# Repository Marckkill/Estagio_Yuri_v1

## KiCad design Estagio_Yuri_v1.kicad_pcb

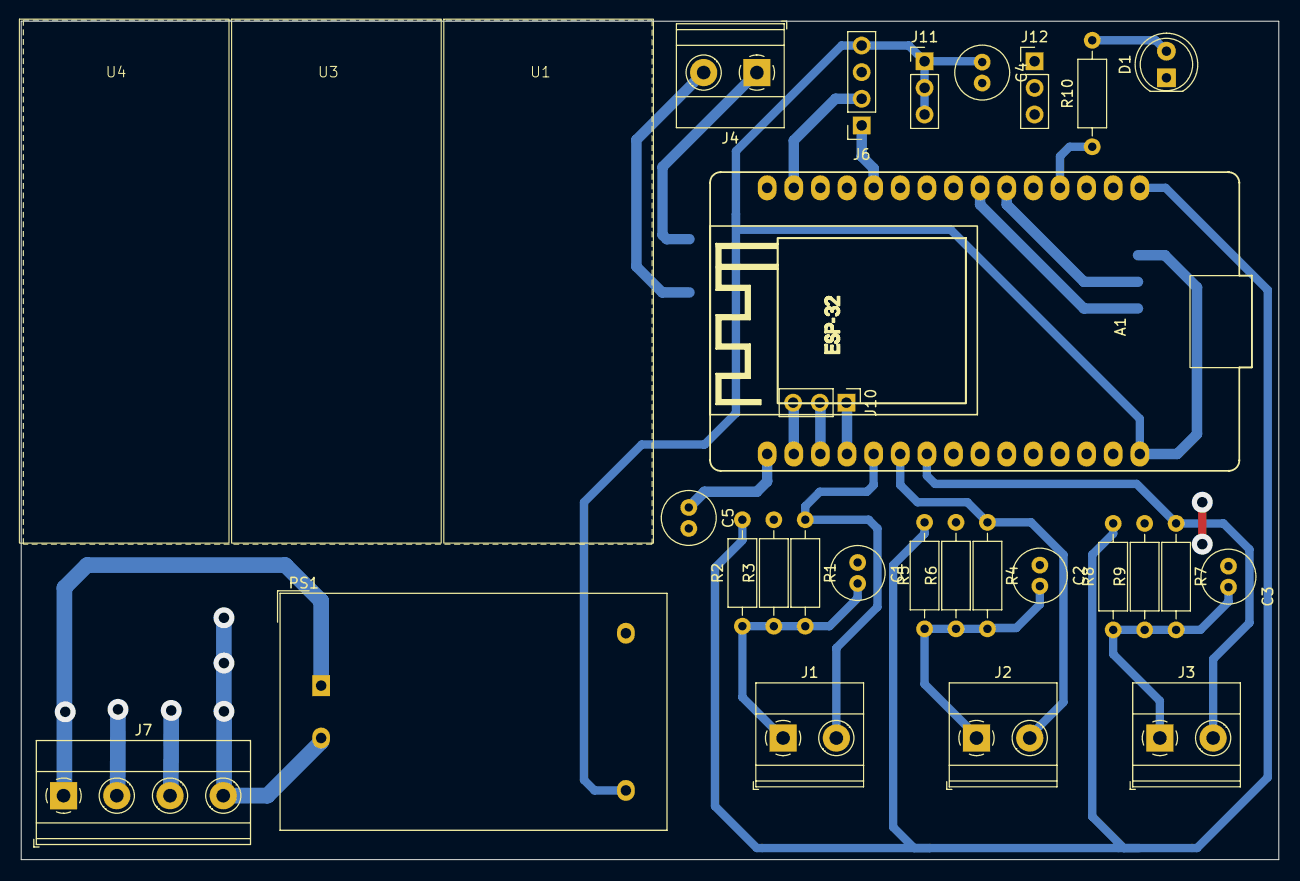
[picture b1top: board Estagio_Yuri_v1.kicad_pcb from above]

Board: 2 copper layers, 120.0 x 80.0 mm, 31 parts (1 on the bottom side), 23 nets.

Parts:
A1: ESP32; DOIT_ESP32_DEVKIT_30Pins
C1, C2, C3: 10u; C_Radial_D5.0mm_H11.0mm_P2.00mm
C4, C5: C; C_Radial_D5.0mm_H11.0mm_P2.00mm
D1: LED; LED_D5.0mm
J1, J2, J3, J4: EASTRON; TerminalBlock_Phoenix_MKDS-1,5-2-5.08_1x02_P5.08mm_Horizont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
J6: DISPLAY; PinSocket_1x04_P2.54mm_Vertical
J7: V_IN; TerminalBlock_Phoenix_MKDS-1,5-4-5.08_1x04_P5.08mm_Horizont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
J10, J11, J12: V_IN; PinHeader_1x03_P2.54mm_Vertical
PS1: HLK-PM03; Converter_ACDC_Hi-Link_HLK-PMxx
R1, R4, R7: 22; R_Axial_DIN0207_L6.3mm_D2.5mm_P10.16mm_Horizontal
R2, R3, R5, R6, R8, R9: 10K; R_Axial_DIN0207_L6.3mm_D2.5mm_P10.16mm_Horizontal
R10: 470; R_Axial_DIN0207_L6.3mm_D2.5mm_P10.16mm_Horizontal
U1, U3, U4: ZMPT101B_MOD; ZMB101-SIZE
U2: XY-017

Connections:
+3.3V: A1.1 (3.3V), R2.2, R5.2, R8.2
+5V: A1.30 (VIN), C4.1, J6.4, J11.1, J11.2, J11.3, PS1.4 (+Vout), U2.5 (VCC)
ADC1_CH0/VP: A1.17 (ADC1_CH0/VP), J10.3
ADC1_CH3/VN: A1.18 (ADC1_CH3/VN), J10.2
ADC1_CH4/D32: A1.21 (ADC1_CH4/D32), J2.2, R4.1
ADC1_CH5/D33: A1.22 (ADC1_CH5/D33), J3.2, R7.1
ADC1_CH6/D34: A1.19 (ADC1_CH6/D34), J10.1
ADC1_CH7/D35: A1.20 (ADC1_CH7/D35), J1.2, R1.1
D2/ADC2_CH2: A1.4 (D2/ADC2_CH2), R10.1
D21/SDA: A1.11 (D21/SDA), J6.1
D22/SCL: A1.14 (D22/SCL), J6.2
EN: A1.16 (EN), C5.1
GND: A1.2 (GND), A1.29 (GND), C1.1, C2.1, C3.1, C4.2, C5.2, D1.1, J6.3, J12.1, J12.2, J12.3, PS1.3 (-Vout), R3.2, R6.2, R9.2, U2.4 (GND)
N: J7.4, PS1.2 (AC/N)
unnamed: D1.2, R10.2
unnamed: C1.2, J1.1, R1.2, R2.1, R3.1
unnamed: C2.2, J2.1, R4.2, R5.1, R6.1
unnamed: C3.2, J3.1, R7.2, R8.1, R9.1
unnamed: J4.1, U2.3 (A+)
unnamed: J4.2, U2.2 (B-)
RX2/GPIO16: A1.6 (RX2/GPIO16), U2.7 (TX)
TX2/GPIO17: A1.7 (TX2/GPIO17), U2.6 (RX)
V_L1: J7.1, PS1.1 (AC/L)
